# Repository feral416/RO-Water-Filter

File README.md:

# Reverse Osmosis Water Filter Controller

## Intro

Project designed to automate home electric RO water filter system that includes intake shutoff valve, pump and optionally automatic flush valve, using microcontroller Arduino Pro Micro(ATmega32U4). Project has low cost, requires minimum components and uses no extra sensors and actuators.

**Aims of the project:**

- Make operation safer.
- Prolong lifespan of valves and pump by eliminating major flaws of pure electric control.
- Prevent extra wear of filters.
- Make diagnostics easier.
- Make it possible to work from unpressurized water source without rewiring.

Basic electric circuit has two sensors for low and high pressure, if pressure is not high and not low respective contacts are closed and power supplied to the actuators: intake shutoff valve, diaphragm pump and automatic flush valve that bypasses drain restriction for short period of time. The major flaw is that low pressure sensor doesn't have deadband at certain low pressure, when sensor is not tripped, starting the pump causes pressure drop and sensor trips which turns off actuators and pressure becomes sufficient again and cycle continues. This self-oscillating process has period less than a second causing major wear to valves and pump mechanics, electrical parts work at inrush current producing excessive heat which in turns can damage the insulation of windings. Second problem is frequent turn on and off caused by opening a tap for a short period of time so closing it will cause pressure to trip high pressure sensor again thus de-energizing the actuators. Third problem is there is no protection from sensors or pump malfunction and accidental leaving the tap open.

## Hardware

Electric schematics made with KiCad, hydraulics diagram made with FluidSIM, PDF versions are available in respective folder.

The main controller is Arduino Pro Micro(ATmega32U4) reads 3 signals from two sensors and a switch, output 3 signals to 2 LEDs and one to actuators, that controlled with logic-level MOSFET. MC is powered from 24V main supply using L7805 linear voltage regulator. User panel consist of: two LEDs- yellow and red, a switch. Diodes are used to protect from kickback voltages. Cap C3 filtering ripple from DC motor operation.

Note that high pressure sensor breaks the circuit so as detected by the MC. It's made intentionally redundant to protect from dangerous pressure to build-up or continuous uncontrolled operation due to controller or MOSFET fault.

Power consumption of the device is 14mA(max) at 24V- 0.336W, 40mA during boot.

## Software

Software is written in PlatformIO with C++ using Arduino framework. Software is compatible with any other Arduino-compatible board.

**Software functions:**

- Monitors state of sensors.
- Prevent operation in undesired conditions: low pressure or too high pressure.
- Prevent indefinite operation due to inability to build up pressure by limiting continuous operation time.
- Prevent frequent turning on/offs caused by low water pressure by adding progressive delay between retries: 10-30-60 minutes
   thus making it self-recoverable condition.
- Prevent frequent operation by requiring high-pressure sensor to stay closed for 30s and making 10m delay between turn-ons.
- Display sensors state and faults.
- Allowing to bypass low pressure sensor, reset the faulty state, bypass waiting between switching on.

Loading program only possible shortly(~12s) after reboot.

In order to save power in program is used power down mode, which uses inaccurate wdt timer with tolerance +-20%, so all time operations will be inaccurate, due to that interval time has to be calibrated to exact used devise. In this project interval increased by 18.3% from default 60 to 71ms. Anyways for that project such time drift isn't critical.

Software has a watchdog to prevent mc to hang during program execution leaving outputs in high state, if program won't respond in 3s mc watchdog will reboot the mc.

## Operation manual

Normal operation doesn't require any user interaction with the controller.

**Front panel**

Front panel yellow LED(H) displays state of high pressure sensor, if continuos on means high pressure is reached or sensor's wire is broken. If the LED flash it signals that maximum operation time is reached(1h), that can be reset by switching switch on-off or turning off/on the power supply.

Front panel red LED(L) displays the state of low pressure sensor, if continuous on means that pressure is low or sensor wire is broken. If the LED flash that means low pressure turned on rapidly and gone quickly, which is faulty state and the controller waits some time to try turn on actuators again. This fault recovers by itself or switching the switch on/off or turning off/on the power supply.

Front panel switch resets faults and turn on the maintenance mode that allows operation without delays and ignores low pressure sensor.

If none of LEDs is on means that program is either waiting in restart delay or actuators work.

Built-in arduino green LED signals that power is on.

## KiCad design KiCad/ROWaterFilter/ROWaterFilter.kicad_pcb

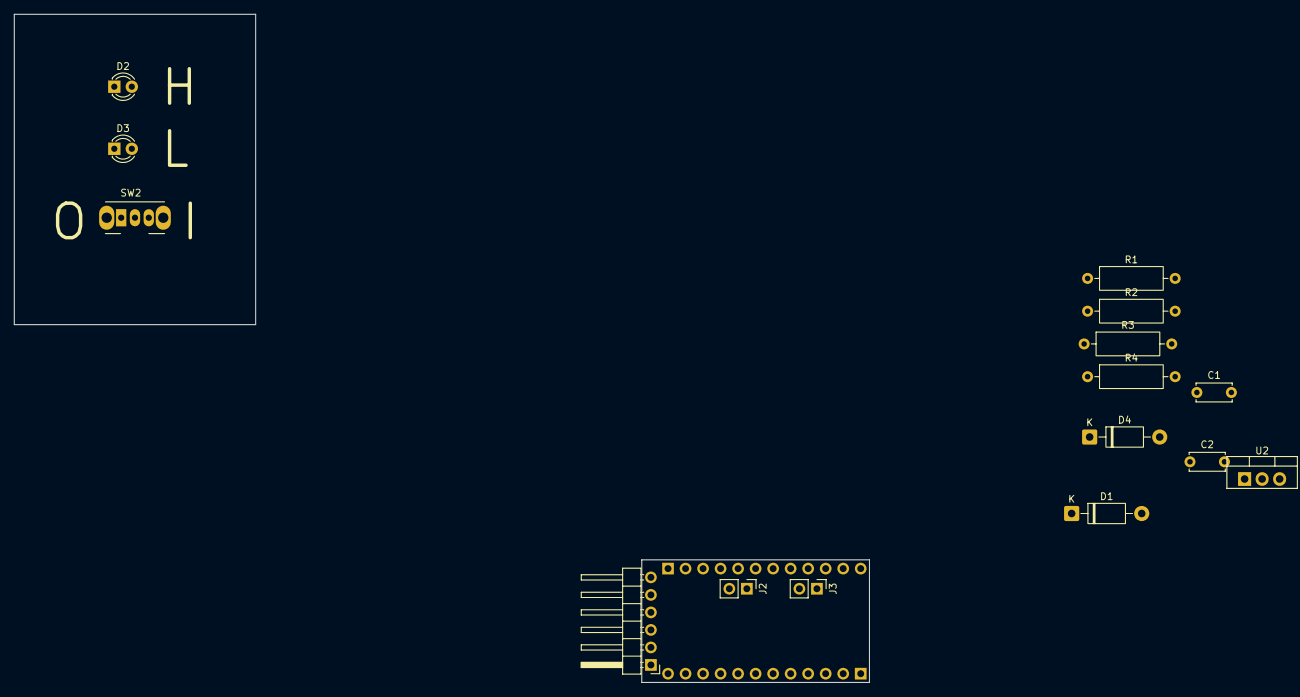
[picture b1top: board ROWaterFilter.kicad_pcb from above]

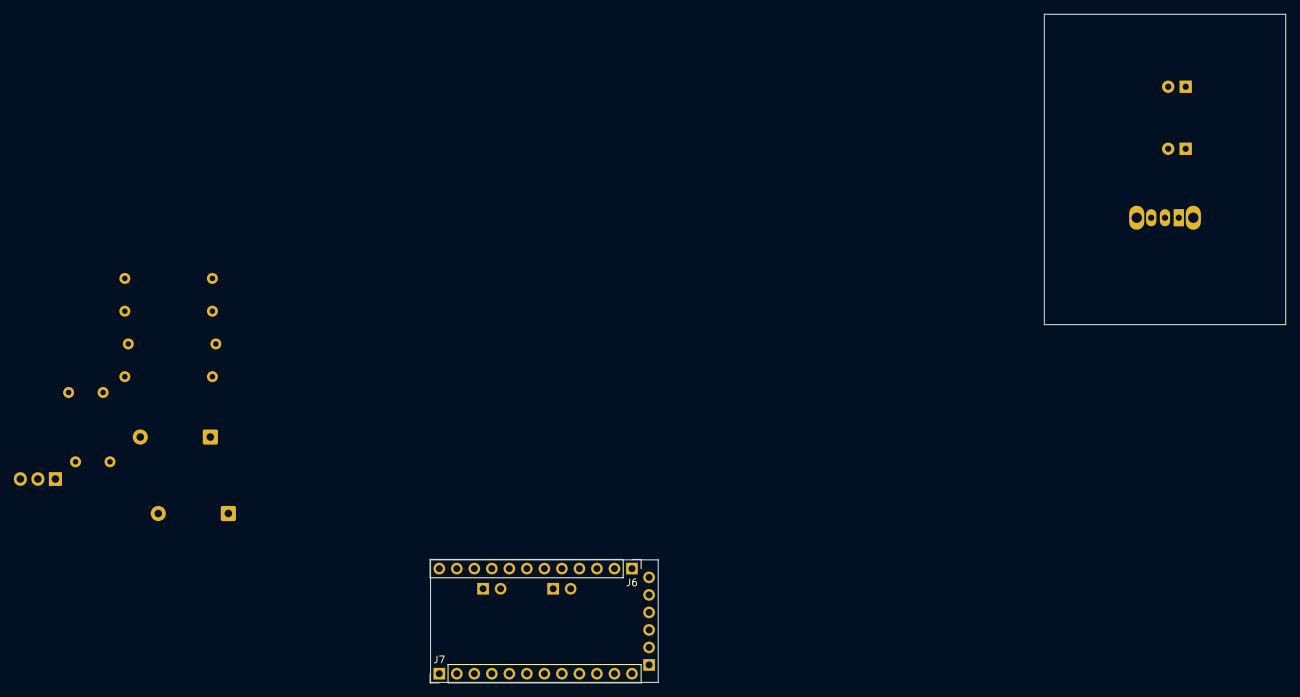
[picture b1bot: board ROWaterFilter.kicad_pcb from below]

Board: 2 copper layers, 17 parts (2 on the bottom side), 12 nets, no tracks yet.

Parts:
C1: 0.33u; C_Disc_D5.0mm_W2.5mm_P5.00mm
C2: 0.1u; C_Disc_D5.0mm_W2.5mm_P5.00mm
D1, D4: 1N4007; D_DO-41_SOD81_P10.16mm_Horizontal
D2: High P; LED_D3.0mm
D3: Low P; LED_D3.0mm
J1: FTDI; PinHeader_1x06_P2.54mm_Horizontal
J2: I2C; PinHeader_1x02_P2.54mm_Vertical
J3: Analog; PinHeader_1x02_P2.54mm_Vertical
J6: Analog; PinHeader_1x12_P2.54mm_Vertical
J7: Digital; PinHeader_1x12_P2.54mm_Vertical
R1, R2, R3: 1k; R_Axial_DIN0309_L9.0mm_D3.2mm_P12.70mm_Horizontal
R4: 10k; R_Axial_DIN0309_L9.0mm_D3.2mm_P12.70mm_Horizontal
SW2: Maintenance mode switch; SW_Slide_SPDT_Angled_CK_OS102011MA1Q
U2: L7805; TO-220-3_Vertical

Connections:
/*D9: J7.9 (Pin_1), SW2.3 (C)
/D4: J7.4 (Pin_6), R3.2
/D7: J7.7 (Pin_3), R2.2
/TX: J1.5, J7.1 (Pin_12)
GND: J1.1, J1.2
unnamed: C1.1, D1.1 (K), U2.1 (IN)
unnamed: D2.2 (A), R2.1
unnamed: D2.1 (K), D3.1 (K), SW2.2 (B)
unnamed: D3.2 (A), R3.1
unnamed: C1.2, C2.1, R4.2, U2.2 (GND)
unnamed: C2.2, U2.3 (OUT)
unnamed: R1.1, R4.1

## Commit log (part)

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2026-03-24 release
2026-03-25 add: manual, description to readme; comments in code
2026-03-26 add: powerdown mode, freeze watchdog
2026-03-26 add: hydraulic diagram
2026-03-26 docs: update readme for clarity
2026-04-06 docs, refactor, feat: readme update, refactor timers in lib, add time calibration function
2026-04-06 docs: hydraulic schematic elements names correctected, minor readme edit
